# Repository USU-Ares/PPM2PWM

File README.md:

# PPM2PWM
All files pertaining to the PPM2PWM device are placed in this repository. These files include: 1. Schematic and PCB KICAD files. 2. MPLABX project in C for firmware.

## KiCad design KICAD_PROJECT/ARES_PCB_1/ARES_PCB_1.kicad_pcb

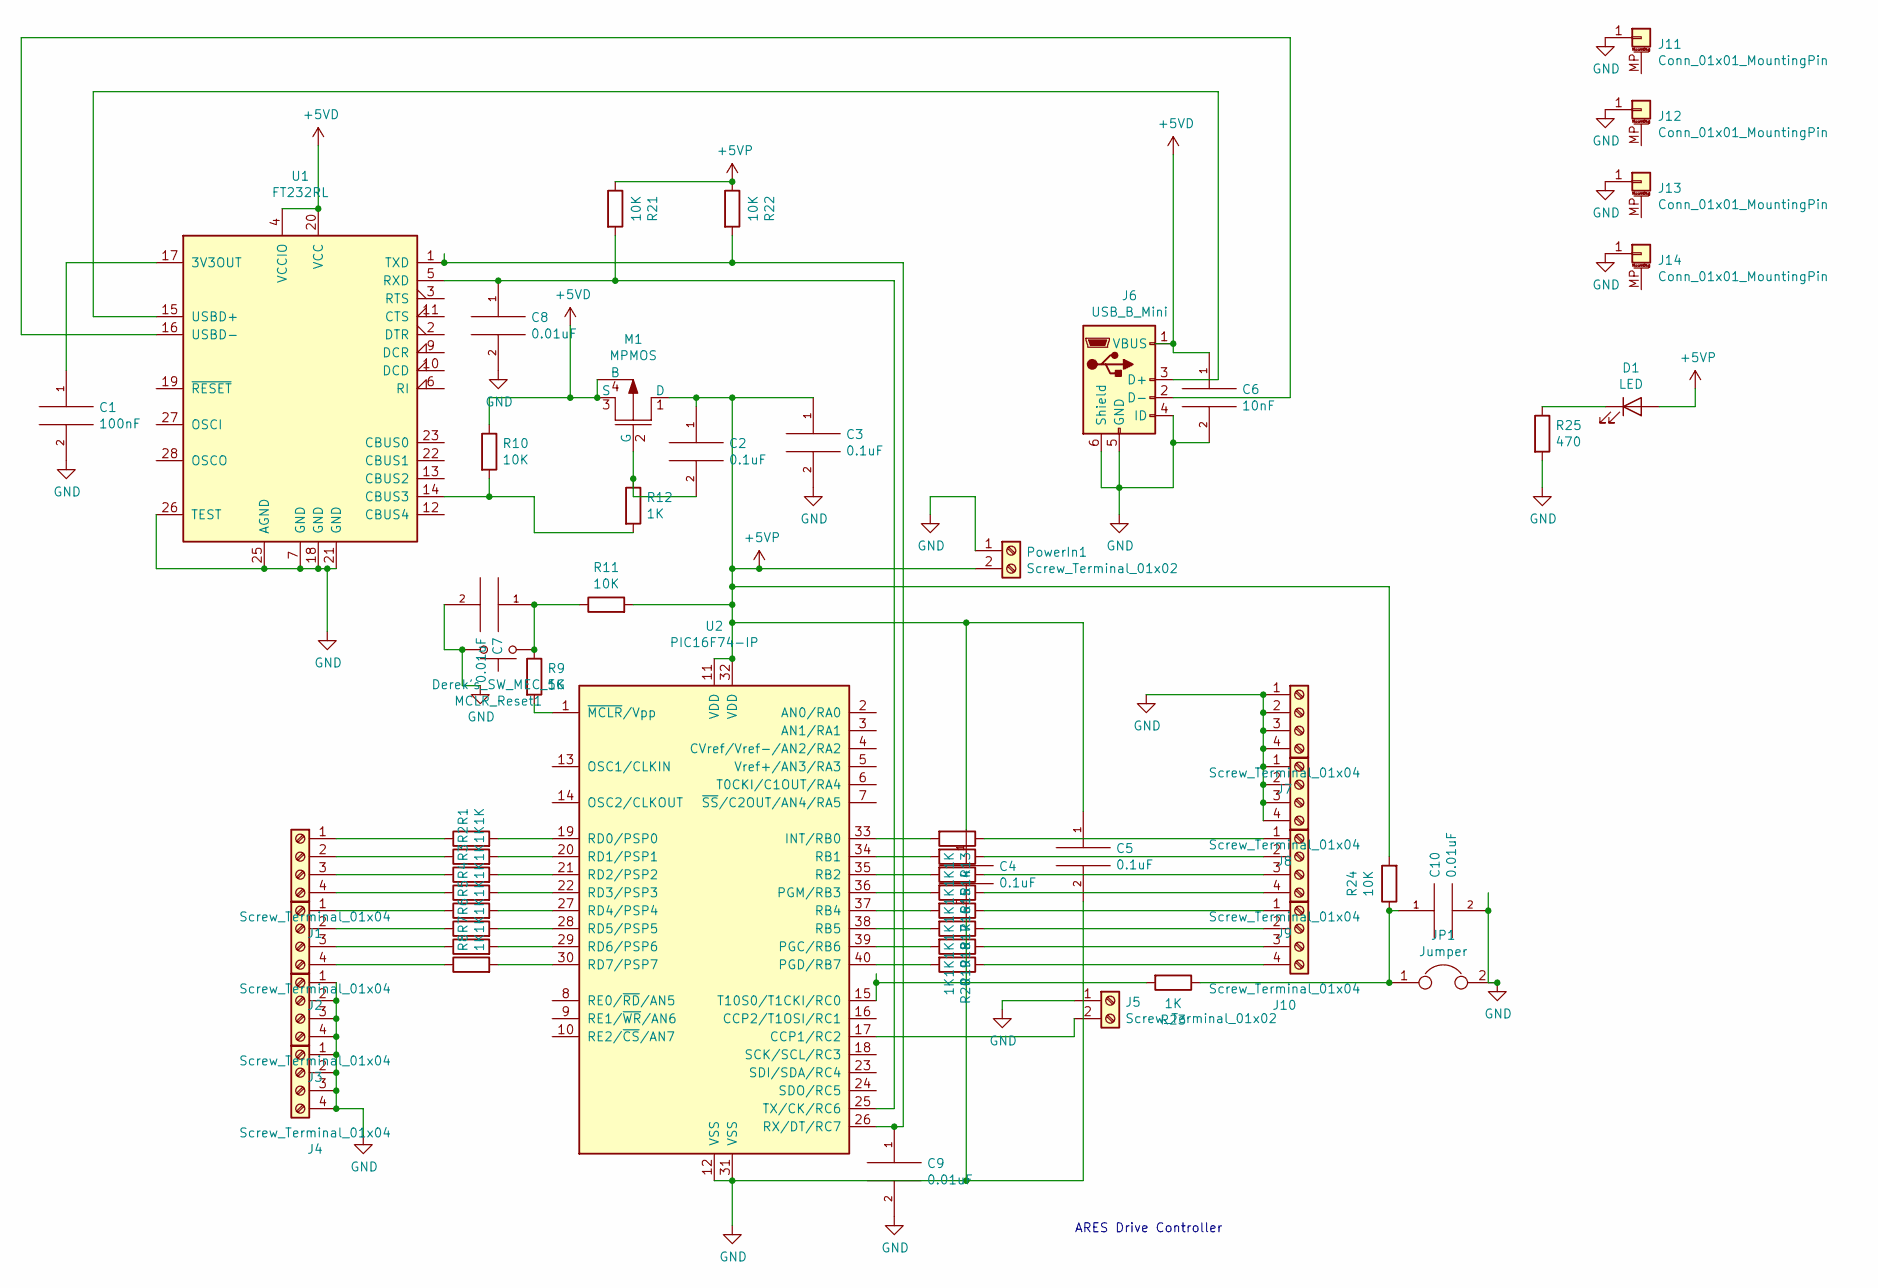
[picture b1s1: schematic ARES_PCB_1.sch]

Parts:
C1: 100nF; CP_Radial_D4.0mm_P2.00mm
C2, C3, C4, C5: 0.1uF; CP_Radial_D4.0mm_P2.00mm
C6: 10nF; CP_Radial_D4.0mm_P2.00mm
C7, C8, C9, C10: 0.01uF; CP_Radial_D4.0mm_P2.00mm
D1: LED; LED_D3.0mm
J1, J2, J3, J4, J7, J8, J9, J10: Screw_Terminal_01x04; JST_EH_B4B-EH-A_1x04_P2.50mm_Vertical
J5: Screw_Terminal_01x02; JST_EH_B2B-EH-A_1x02_P2.50mm_Vertical
J6: USB_B_Mini; USB_Mini-B_Wuerth_Horizontal_1.70mm(0.0625in)_spacing
J11, J12, J13, J14: Conn_01x01_MountingPin; Derek's_Banana_Jack_1Pin
JP1: Jumper; PinHeader_1x02_P2.54mm_Vertical
M1: MPMOS; A19T_Handsoldering
MCLR_Reset1: Derek's_SW_MEC_5G; Derek's_SW_PUSH_8.89mm_H4.3mm
PowerIn1: Screw_Terminal_01x02; JST_EH_B2B-EH-A_1x02_P2.50mm_Vertical
R1, R2, R3, R4, R5, R6, R7, R8, R9, R12, R13, R14, R15, R16, R17, R18, R19, R20, R23: 1K; R_Axial_DIN0207_L6.3mm_D2.5mm_P10.16mm_Horizontal
R10, R11, R21, R22, R24: 10K; R_Axial_DIN0207_L6.3mm_D2.5mm_P10.16mm_Horizontal
R25: 470; R_Axial_DIN0207_L6.3mm_D2.5mm_P10.16mm_Horizontal
U1: FT232RL; SSOP-28_5.3x10.2mm_P0.65mm
U2: PIC16F74-IP; DIP-40_W15.24mm_LongPads

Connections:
+5VD: C6.1, J6.1 (VBUS), M1.3 (S), M1.4 (B), R10.1, U1.4 (VCCIO), U1.20 (VCC)
+5VP: C2.1, C3.1, C4.1, C5.1, D1.2 (A), M1.1 (D), PowerIn1.2, R11.2, R21.1, R22.1, R24.2, U2.11 (VDD), U2.32 (VDD)
GND: C1.2, C3.2, C4.2, C5.2, C6.2, C7.2, C8.2, C9.2, C10.2, J3.1, J3.2, J3.3, J3.4, J4.1, J4.2, J4.3, J4.4, J5.1, J6.4 (ID), J6.5 (GND), J6.6 (Shield), J7.1, J7.2, J7.3, J7.4, J8.1, J8.2, J8.3, J8.4, J11.1, J12.1, J13.1, J14.1, JP1.2, MCLR_Reset1.2 (Passive), PowerIn1.1, R25.2, U1.7 (GND), U1.18 (GND), U1.21 (GND), U1.25 (AGND), U1.26 (TEST), U2.12 (VSS), U2.31 (VSS)
unnamed: C1.1, U1.17 (3V3OUT)
unnamed: C2.2, M1.2 (G), R12.1
unnamed: C7.1, MCLR_Reset1.1 (Active), R9.1, R11.1
unnamed: C8.1, R21.2, U1.5 (RXD), U2.25 (TX/CK/RC6)
unnamed: C9.1, R22.2, U1.1 (TXD), U2.26 (RX/DT/RC7)
unnamed: C10.1, JP1.1, R23.1, R24.1
unnamed: D1.1 (K), R25.1
unnamed: J1.1, R1.1
unnamed: J1.2, R2.1
unnamed: J1.3, R3.1
unnamed: J1.4, R4.1
unnamed: J2.1, R5.1
unnamed: J2.2, R6.1
unnamed: J2.3, R7.1
unnamed: J2.4, R8.1
unnamed: J5.2, U2.17 (CCP1/RC2)
unnamed: J6.2 (D-), U1.16 (USBD-)
unnamed: J6.3 (D+), U1.15 (USBD+)
unnamed: J9.1, R13.1
unnamed: J9.2, R14.1
unnamed: J9.3, R15.1
unnamed: J9.4, R16.1
unnamed: J10.1, R17.1
unnamed: J10.2, R18.1
unnamed: J10.3, R19.1
unnamed: J10.4, R20.1
unnamed: R1.2, U2.19 (RD0/PSP0)
unnamed: R2.2, U2.20 (RD1/PSP1)
unnamed: R3.2, U2.21 (RD2/PSP2)
unnamed: R4.2, U2.22 (RD3/PSP3)
unnamed: R5.2, U2.27 (RD4/PSP4)
unnamed: R6.2, U2.28 (RD5/PSP5)
unnamed: R7.2, U2.29 (RD6/PSP6)
unnamed: R8.2, U2.30 (RD7/PSP7)
unnamed: R9.2, U2.1 (~MCLR~/Vpp)
unnamed: R10.2, R12.2, U1.14 (CBUS3)
unnamed: R13.2, U2.33 (INT/RB0)
unnamed: R14.2, U2.34 (RB1)
unnamed: R15.2, U2.35 (RB2)
unnamed: R16.2, U2.36 (PGM/RB3)
unnamed: R17.2, U2.37 (RB4)
unnamed: R18.2, U2.38 (RB5)
unnamed: R19.2, U2.39 (PGC/RB6)
unnamed: R20.2, U2.40 (PGD/RB7)
unnamed: R23.2, U2.15 (T10S0/T1CKI/RC0)

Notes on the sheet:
ARES Drive Controller

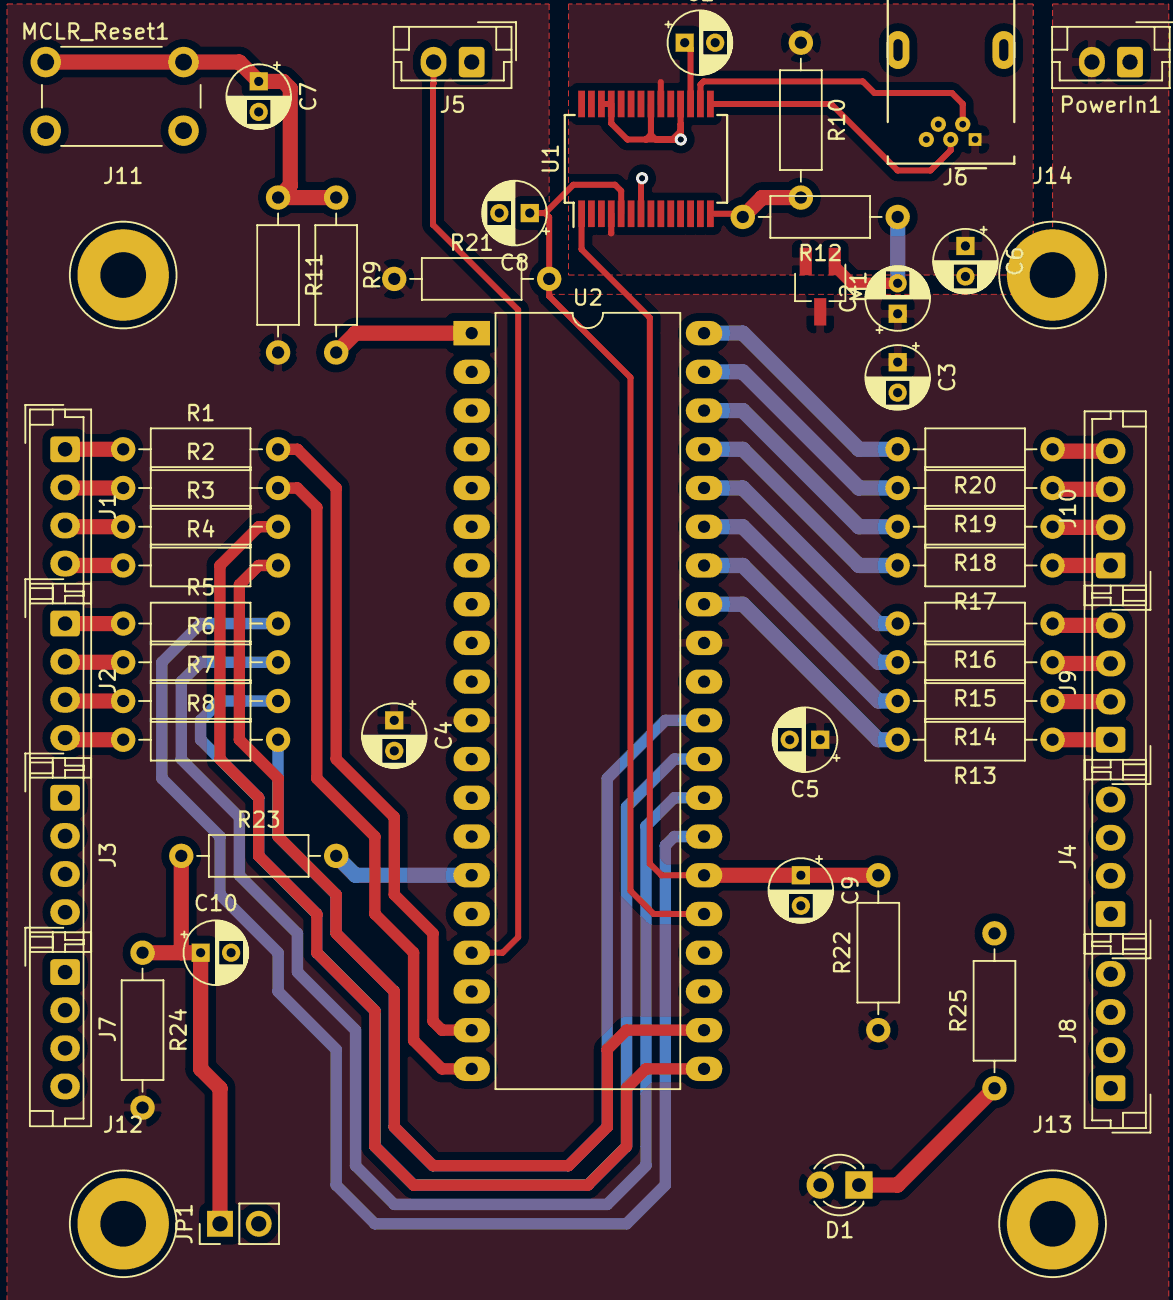
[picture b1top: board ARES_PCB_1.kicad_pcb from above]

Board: 2 copper layers, 56 parts (0 on the bottom side), 48 nets.
